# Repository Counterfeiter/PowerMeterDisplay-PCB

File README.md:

PowerMeter EADOG Display Extension Schematic and PCB Files
==============

License
--------------
OSH - GPLv2

Software
--------------
Free Version of CADSoft Eagle v6 (.1)

Included
--------------
- versions history
- schematic
- PCB design
- Images

Schematic:
--------------

Board design:
--------------

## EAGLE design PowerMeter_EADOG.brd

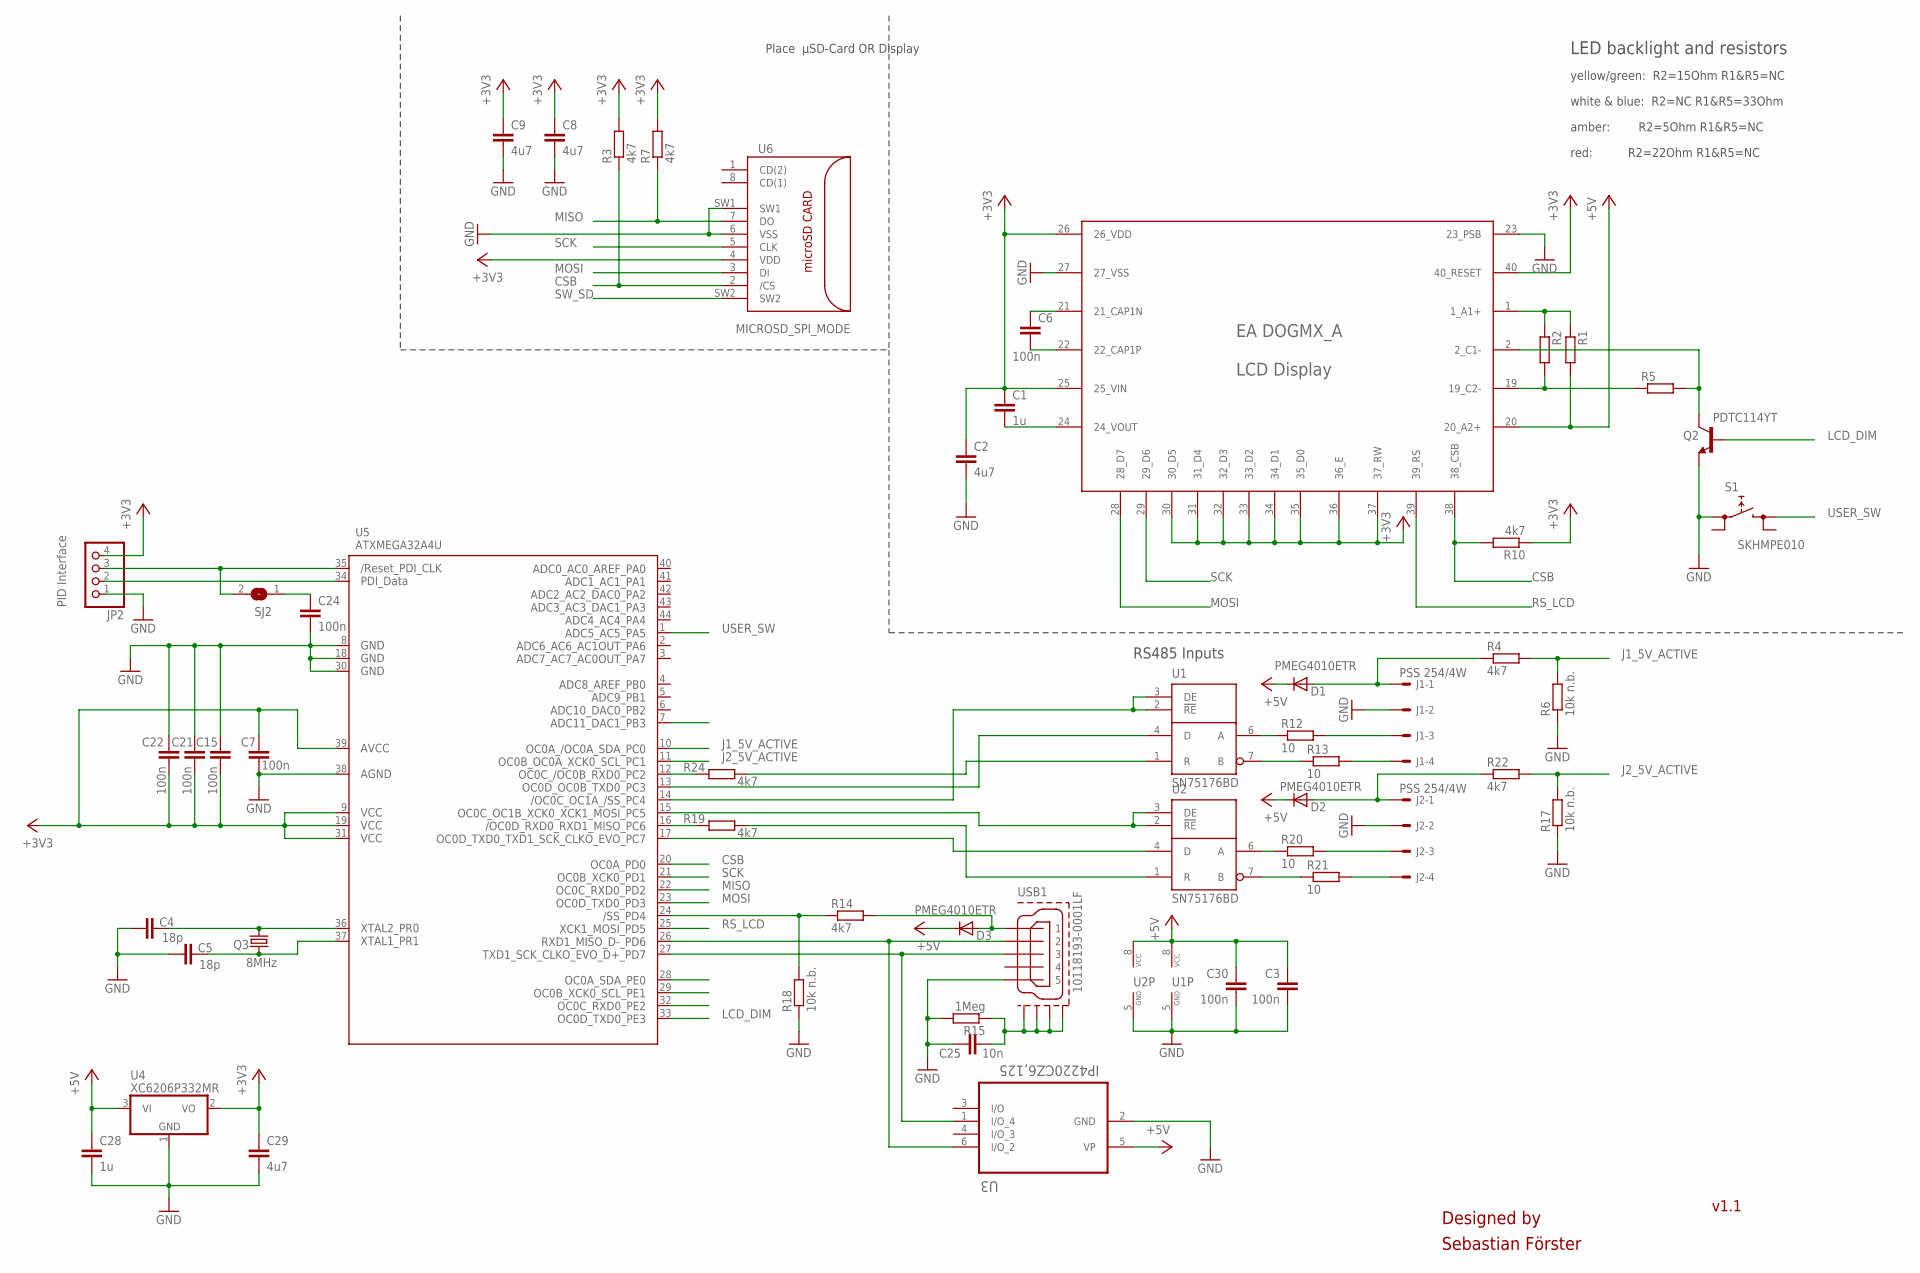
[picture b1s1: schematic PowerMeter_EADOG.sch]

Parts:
C1, C28: 1u; C0603
C2, C8, C9, C29: 4u7; C0603
C3, C6, C7, C15, C21, C22, C24, C30: 100n; C0603
C4, C5: 18p; C0603
C25: 10n; C0603
D1, D2, D3: PMEG4010ETR; SOD123
J1, J2: PSS 254/4W; 6410-04
JP2: PINHD-1X4_2.00; 1X04M
LCD1: DOGM162X-AX; EA_DOGM
Q2: PDTC114YT; SOT23
Q3: 8MHz; HC49UP
R1, R2, R5: R-EU_R0603; R0603
R3, R4, R7, R10, R14, R19, R22, R24: 4k7; R0603
R6, R17, R18: 10k n.b.; R0603
R12, R13, R20, R21: 10; R0603
R15: 1Meg; R0603
S1: SKHMPE010; SKHMPXE010
SJ2: SJ
U1, U2: SN75176BD; SO-08
U3: IP4220CZ6,125; SOT95P275X110-6N
U4: XC6206P332MR; SOT23
U5: ATXMEGA32A4U; TQFP44
U6: MICROSD_SPI_MODE; MICRO_SD_CONNECTOR
USB1: 10118193-0001LF; MOLEX-47364-0001

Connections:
+3V3: C1.1, C2.1, C7.1, C8.1, C9.1, C15.2, C21.2, C22.2, C29.1, JP2.4, LCD1.25 (25_VIN), LCD1.26 (26_VDD), LCD1.30 (30_D5), LCD1.31 (31_D4), LCD1.32 (32_D3), LCD1.33 (33_D2), LCD1.34 (34_D1), LCD1.35 (35_D0), LCD1.36 (36_E), LCD1.37 (37_RW), LCD1.40 (40_RESET), R3.2, R7.2, R10.1, U4.2 (VO), U5.9 (VCC1), U5.19 (VCC2), U5.31 (VCC3), U5.39 (AVCC), U6.4 (VDD)
+5V: C3.1, C28.1, C30.1, D1.C, D2.C, D3.C, LCD1.20 (20_A2+), R1.2, U1.8 (VCC), U2.8 (VCC), U3.5 (VP), U4.3 (VI)
CSB: LCD1.38 (38_CSB), R3.1, R10.2, U5.20 (PD0), U6.2 (/CS)
GND: C2.2, C3.2, C4.1, C5.1, C7.2, C8.2, C9.2, C15.1, C21.1, C22.1, C24.2, C25.1, C28.2, C29.2, C30.2, J1.2, J2.2, JP2.1, LCD1.23 (23_PSB), LCD1.27 (27_VSS), Q2.2 (E), R6.1, R15.2, R17.1, R18.1, S1.1 (1.1), U1.5 (GND), U2.5 (GND), U3.2 (GND), U4.1 (GND), U5.8 (GND1), U5.18 (GND2), U5.30 (GND3), U5.38 (AGND), U6.6 (VSS), U6.SW1, USB1.5
J1_5V_ACTIVE: R4.2, R6.2, U5.10 (PC0)
J2_5V_ACTIVE: R17.2, R22.2, U5.11 (PC1)
LCD_DIM: Q2.1 (B), U5.33 (PE3)
MISO: R7.1, U5.22 (PD2), U6.7 (DO)
MMM: D2.A, J2.1, R22.1
MOSI: LCD1.28 (28_D7), U5.23 (PD3), U6.3 (DI)
unnamed: R21.1, U2.7 (B)
unnamed: R20.1, U2.6 (A)
unnamed: R19.2, U2.1 (R)
unnamed: LCD1.2 (2_C1-), Q2.3 (C), R5.2
unnamed: U2.2 (!RE), U2.3 (DE), U5.15 (PC5)
unnamed: U2.4 (D), U5.17 (PC7)
unnamed: J2.3, R20.2
unnamed: J2.4, R21.2
unnamed: LCD1.19 (19_C2-), R2.2, R5.1
unnamed: LCD1.1 (1_A1+), R1.1, R2.1
unnamed: R19.1, U5.16 (PC6)
unnamed: U1.2 (!RE), U1.3 (DE), U5.14 (PC4)
unnamed: JP2.3, SJ2.2, U5.35 (RESET)
unnamed: C4.2, Q3.1, U5.36 (PR0)
unnamed: JP2.2, U5.34 (PDI_DATA)
unnamed: R14.1, R18.2, U5.24 (PD4)
unnamed: C5.2, Q3.2, U5.37 (PR1)
unnamed: R13.1, U1.7 (B)
unnamed: R12.1, U1.6 (A)
unnamed: C25.2, R15.1, USB1.GND1, USB1.GND2, USB1.GND3, USB1.GND4
unnamed: U3.6 (I/O_2), U5.26 (PD6), USB1.2
unnamed: U3.1 (I/O_4), U5.27 (PD7), USB1.3
unnamed: C1.2, LCD1.24 (24_VOUT)
unnamed: C6.2, LCD1.22 (22_CAP1P)
unnamed: C6.1, LCD1.21 (21_CAP1N)
unnamed: C24.1, SJ2.1
unnamed: D3.A, R14.2, USB1.1
unnamed: R24.2, U1.1 (R)
unnamed: U1.4 (D), U5.13 (PC3)
unnamed: J1.3, R12.2
unnamed: J1.4, R13.2
unnamed: R24.1, U5.12 (PC2)
NNN: D1.A, J1.1, R4.1
RS_LCD: LCD1.39 (39_RS), U5.25 (PD5)
SCK: LCD1.29 (29_D6), U5.21 (PD1), U6.5 (CLK)
SW_SD: U5.28 (PE0), U6.SW2
USER_SW: S1.3 (2.3), U5.1 (PA5)

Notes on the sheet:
Designed by
Sebastian Förster
yellow/green: R2=15Ohm R1&R5=NC
LED backlight and resistors
white & blue: R2=NC R1&R5=33Ohm
amber: R2=5Ohm R1&R5=NC
red: R2=22Ohm R1&R5=NC
PID Interface
RS485 Inputs
v1.1
Place µSD-Card OR Display

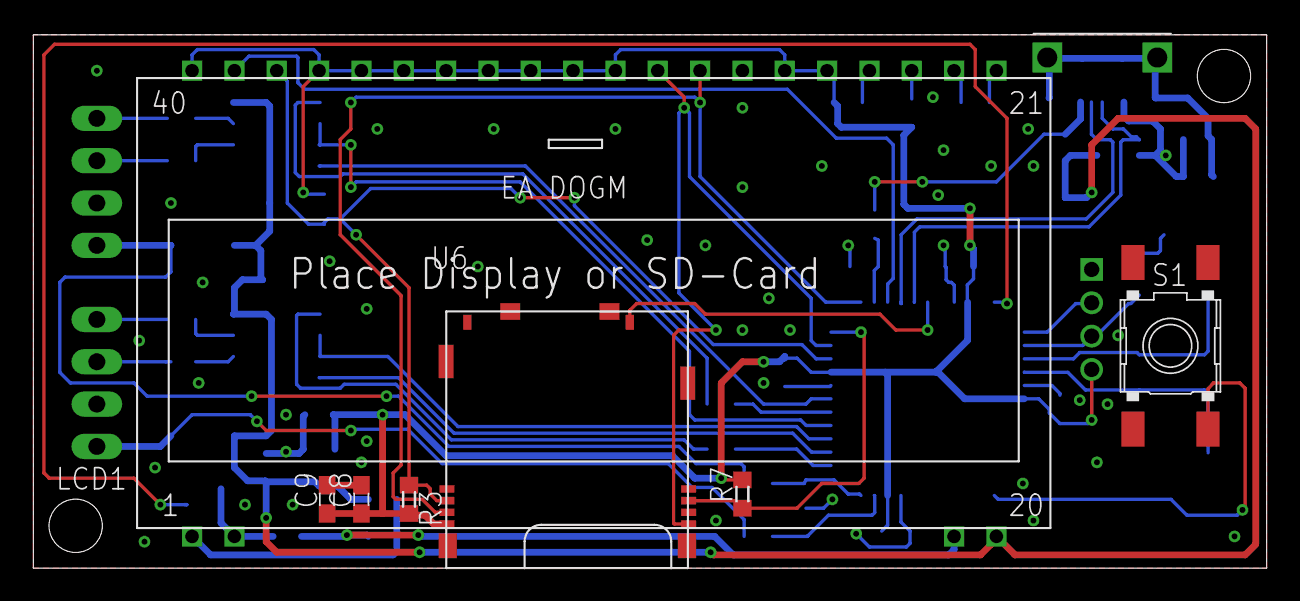
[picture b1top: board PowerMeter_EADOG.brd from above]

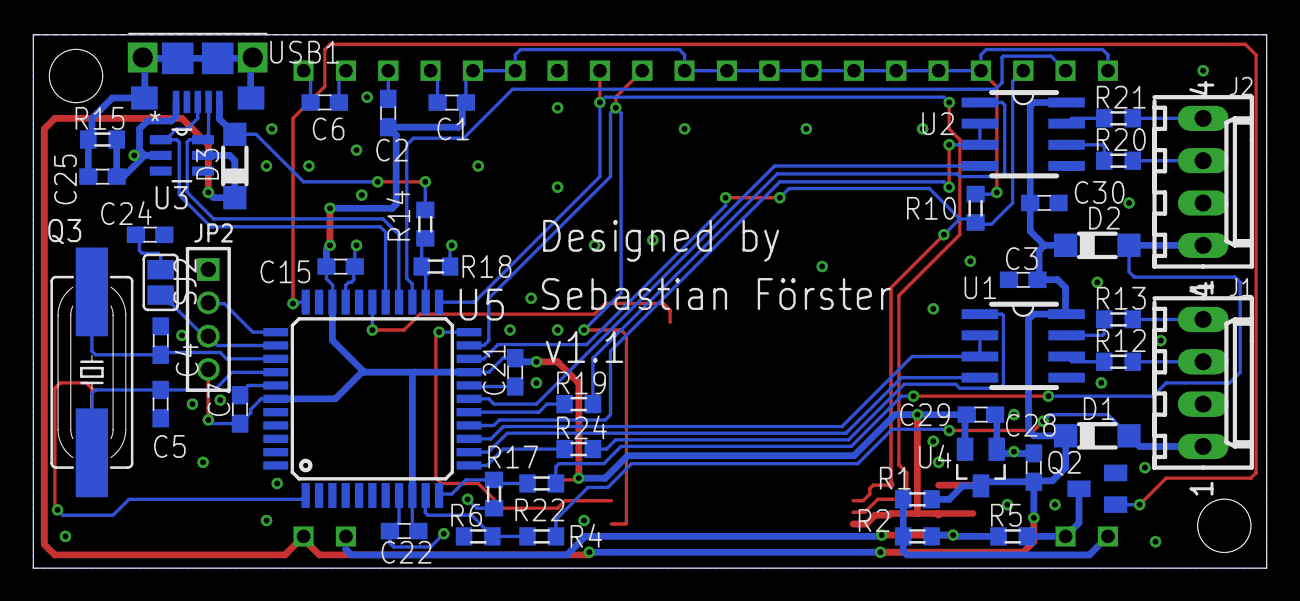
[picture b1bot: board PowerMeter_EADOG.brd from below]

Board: 2 copper layers, 74.0 x 32.1 mm, 54 parts (47 on the bottom side), 47 nets.

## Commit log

2015-07-03 adding license file
2015-08-02 - adding SD-Card option - moving push button to the center
2016-02-09 - added BOM
